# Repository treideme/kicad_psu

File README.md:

# Sample Project 2 for KiCad like a Pro
 * See the course [here](https://www.udemy.com/course/kicad-like-a-pro-3e/).

This project exemplifies the fundamentals of KiCad EDA for a simple 2 layer board.

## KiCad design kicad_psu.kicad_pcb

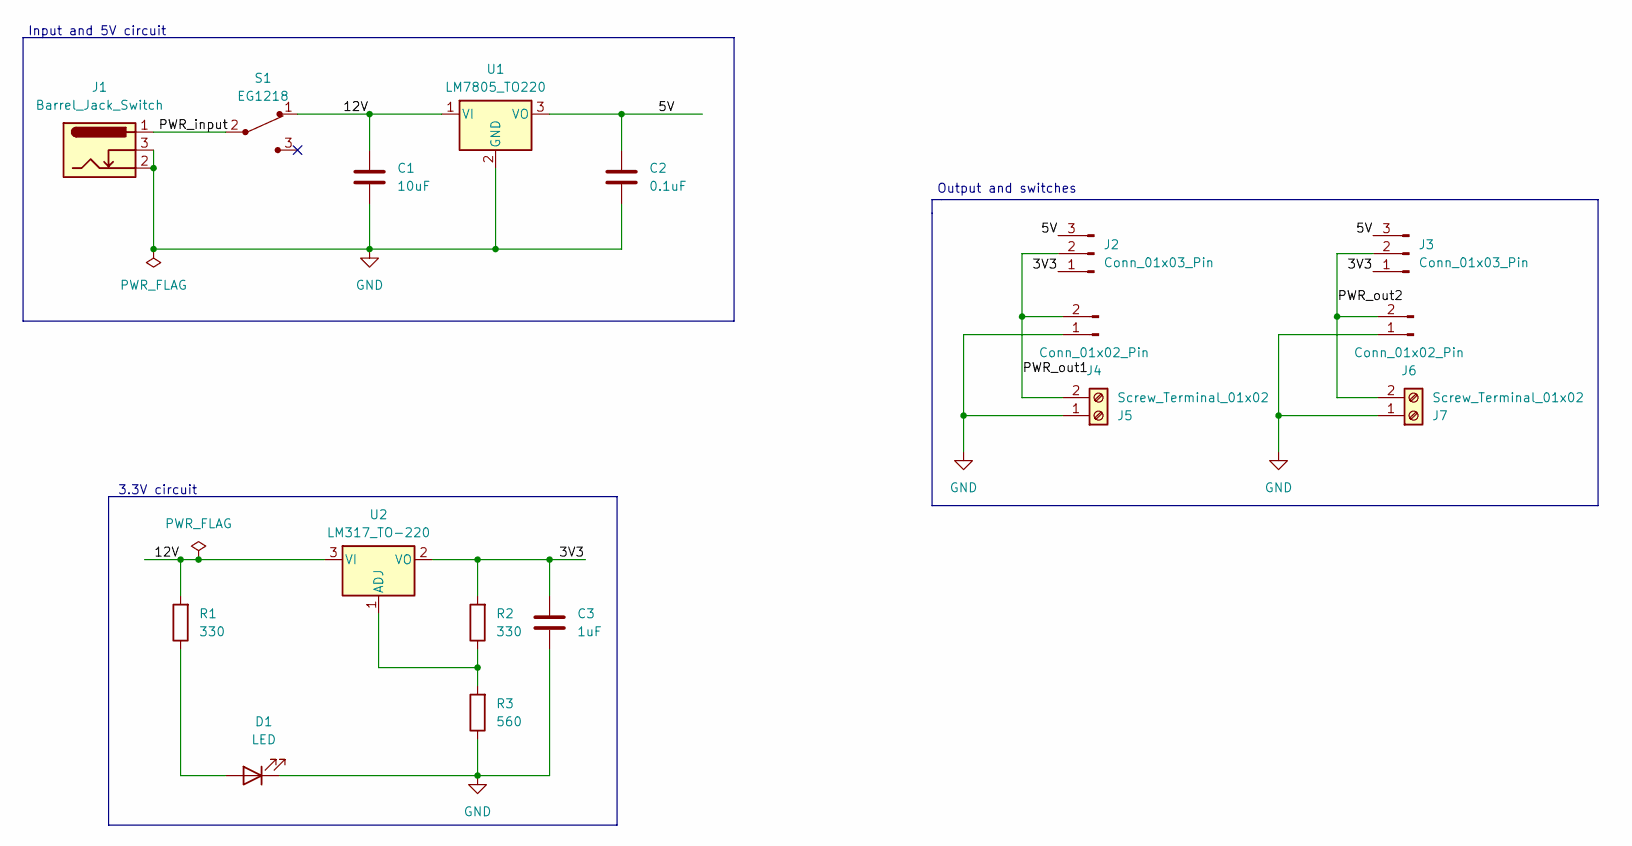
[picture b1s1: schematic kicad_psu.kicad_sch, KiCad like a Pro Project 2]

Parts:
C1: 10uF; C_Disc_D3.0mm_W1.6mm_P2.50mm
C2: 0.1uF; C_Disc_D3.0mm_W1.6mm_P2.50mm
C3: 1uF; C_Disc_D3.0mm_W1.6mm_P2.50mm
D1: LED; LED_D5.0mm
J1: Barrel_Jack_Switch; BarrelJack_Horizontal
J2, J3: Conn_01x03_Pin; PinHeader_1x03_P2.54mm_Vertical
J4, J6: Conn_01x02_Pin; PinHeader_1x02_P2.54mm_Vertical
J5, J7: Screw_Terminal_01x02; TerminalBlock_bornier-2_P5.08mm
R1, R2: 330; R_Axial_DIN0204_L3.6mm_D1.6mm_P7.62mm_Horizontal
R3: 560; R_Axial_DIN0204_L3.6mm_D1.6mm_P7.62mm_Horizontal
S1: EG1218; Switch_Slide_11.6x4mm_EG1218; MPN EG1218; Digi-Key_PN EG1903-ND
U1: LM7805_TO220; TO-220-3_Vertical
U2: LM317_TO-220; TO-220-3_Vertical

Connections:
/3V3: C3.1, J2.1, J3.1, R2.2, U2.2 (VO)
/5V: C2.1, J2.3, J3.3, U1.3 (VO)
/12V: C1.1, R1.2, S1.1, U1.1 (VI), U2.3 (VI)
/PWR_input: J1.1, S1.2
/PWR_out1: J2.2, J4.2, J5.2
/PWR_out2: J3.2, J6.2, J7.2
GND: C1.2, C2.2, C3.2, D1.1 (K), J1.2, J1.3, J4.1, J5.1, J6.1, J7.1, R3.1, U1.2 (GND)
unnamed: D1.2 (A), R1.1
unnamed: R2.1, R3.2, U2.1 (ADJ)

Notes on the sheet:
Input and 5V circuit
3.3V circuit
Output and switches

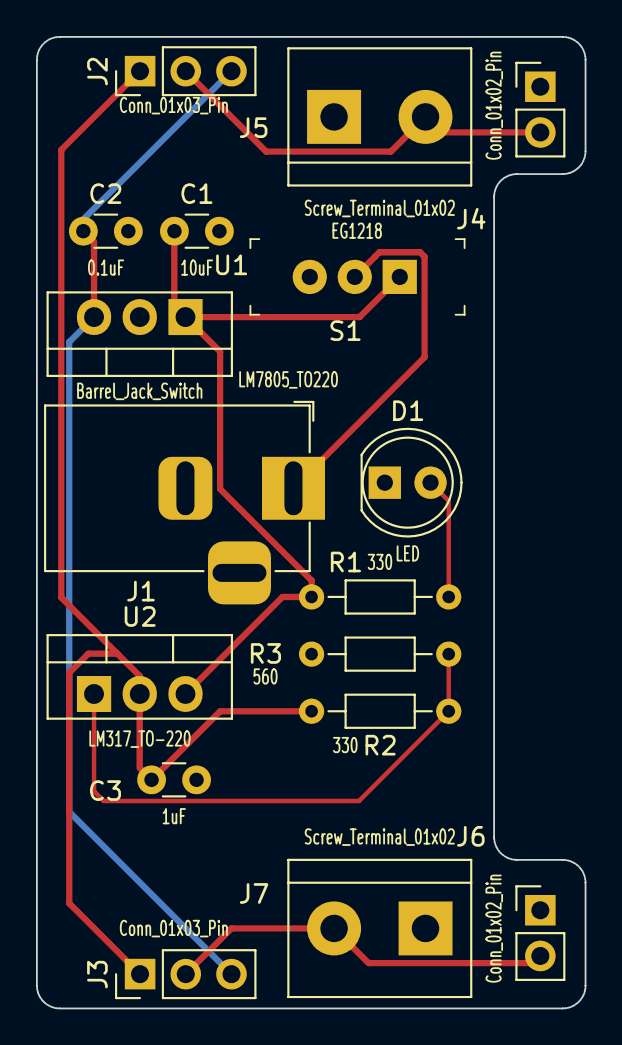
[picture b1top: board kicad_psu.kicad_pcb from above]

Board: 2 copper layers, 30.5 x 54.0 mm, 17 parts (0 on the bottom side), 9 nets.

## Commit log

2023-11-02 Finished PSU without logos
2023-11-07 Gerbers update
